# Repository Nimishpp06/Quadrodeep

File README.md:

# QuadroDeep — Smart Attendance System

> **K. J. Somaiya Institute of Technology** — Academic IoT Project

A full-stack IoT attendance management system for academic lab environments. Combines **ESP32-based hardware** (RFID + Fingerprint) with a **Node.js backend** and **role-based web dashboards** for students, professors, and administrators.

---

## Table of Contents

- [Architecture](#architecture)
- [Features](#features)
- [Tech Stack](#tech-stack)
- [Hardware Pinout](#hardware-pinout)
- [Project Structure](#project-structure)
- [Getting Started](#getting-started)
- [Configuration](#configuration)
- [API Endpoints](#api-endpoints)
- [Team](#team)

---

## Architecture

```
┌─────────────────────────────────────────────────────────┐
│                    Frontend (Browser)                    │
│  Student Dashboard · Professor Dashboard · Admin View    │
└──────────────────────┬──────────────────────────────────┘
                       │ HTTP REST
┌──────────────────────▼──────────────────────────────────┐
│              Node.js Backend (Express)                   │
│  Authentication · Analytics · Session Management · MQTT  │
└──────┬───────────────────────────────┬──────────────────┘
       │ MQTT Pub/Sub                  │ REST
┌──────▼──────┐                 ┌──────▼──────────────────┐
│  ESP32 Node │  ◄──────────── │     Supabase (PostgreSQL) │
│  (RFID+FP)  │  light sleep   │  Attendance · Users · Labs │
└─────────────┘   wake-on-IR   └─────────────────────────┘
```

---

## Features

### Student View
- **Attendance gauge** with color-coded eligibility (≥75% green, <75% red)
- **"Can miss" counter** — how many more classes before falling below threshold
- **Punctuality tracking** — on-time vs late arrival breakdown
- **Verification mode chart** — RFID vs Fingerprint preference
- **Check-in history** — last 20 entries with status badges

### Professor View
- **Live session turnout** — present / total per session
- **Attendance trends** — 30-day line chart
- **Mode adoption pie** — RFID vs Fingerprint usage
- **At-risk flagging** — students with >15% attendance drop over 2 weeks
- **Arrival heatmap** — time-of-day distribution

### Admin View
- **Device fleet monitor** — online / offline / sleep per lab
- **Hardware alerts** — low memory, sensor errors, MQTT drops
- **Enrollment matrix** — students onboarded vs RFID vs biometric
- **Bypass audit log** — force-initialized sessions outside timetable
- **Global attendance rate** with most-utilized lab

### Hardware Capabilities
- Dual-factor authentication (RFID + Fingerprint)
- Light sleep after 5 min idle — wakes on IR motion or button press
- UART state preserved across sleep (no fingerprint re-init)
- Common-anode RGB status indicator
- Standalone offline queue with JSON storage on SPIFFS

---

## Tech Stack

| Layer | Technology |
|-------|-----------|
| **Firmware** | Arduino / C++ (ESP32) |
| **Backend** | Node.js + Express |
| **Database** | Supabase (PostgreSQL) |
| **Frontend** | Vanilla JS + Chart.js |
| **Messaging** | MQTT (Mosquitto) |
| **Biometrics** | R307 / AS608 Fingerprint Scanner |
| **RFID** | MFRC522 |
| **Display** | I2C LCD 16×2 |
| **Power** | Light sleep (ESP32 deep sleep variant) |

---

## Hardware Pinout

| Component | ESP32 Pin | Bus |
|-----------|-----------|-----|
| RFID RST | GPIO 4 | — |
| RFID MISO | GPIO 19 | SPI |
| RFID MOSI | GPIO 23 | SPI |
| RFID SCK | GPIO 18 | SPI |
| RFID SDA/SS | GPIO 5 | SPI |
| Fingerprint RX (ESP TX2) | GPIO 17 | UART2 |
| Fingerprint TX (ESP RX2) | GPIO 16 | UART2 |
| Buzzer | GPIO 14 | — |
| IR / PIR Motion | GPIO 33 | — (wake source) |
| Push Button | GPIO 32 | — (wake source) |
| I2C SDA | GPIO 21 | I2C |
| I2C SCL | GPIO 22 | I2C |
| RGB Red | GPIO 27 | Common anode |
| RGB Green | GPIO 26 | Common anode |
| RGB Blue | GPIO 25 | Common anode |

---

## Project Structure

```
QuadroDeep/
├── QuadroDeep_Node/          # ESP32 firmware
│   ├── QuadroDeep_Node.ino   # Main state machine
│   ├── config.h              # Pins, WiFi, MQTT, API base
│   ├── hardware.h            # Init / wake / sleep helpers
│   ├── wifi_manager.h        # WiFi provisioning
│   ├── storage.h             # SPIFFS offline queue
│   └── device_base64.h       # Base64 fingerprint templates
├── backend/                  # Node.js server
│   ├── server.js             # Express app + routes
│   ├── jobs/                 # Cron jobs (reminders)
│   ├── services/             # Notification service
│   ├── templates/            # Email templates
│   ├── utils/                # Helpers (Resend, retry)
│   ├── package.json
│   └── .env.example          # Required environment variables
├── index.html                # Web dashboard
├── QuadroDeep-Logo.png
└── somaiya-logo.png
```

---

## Getting Started

### Prerequisites

- Node.js v18+
- Supabase (PostgreSQL) project
- Mosquitto MQTT broker
- ESP32 with Arduino IDE
- R307 / AS608 fingerprint sensor + MFRC522 RFID module

### Backend

```bash
cd backend
cp .env.example .env    # Edit with your credentials
npm install
node server.js
```

### ESP32 Firmware

1. Open `QuadroDeep_Node/QuadroDeep_Node.ino` in Arduino IDE
2. Install libraries: `MFRC522`, `Adafruit_Fingerprint`, `LiquidCrystal_I2C`, `PubSubClient`, `ArduinoJson`
3. Edit `config.h`:
   - Set `WIFI_SSID` / `WIFI_PASSWORD`
   - Set `API_BASE` to your backend IP
   - Set `MQTT_BROKER` to your broker IP
4. Upload to ESP32

### Frontend

Serve `index.html` via Live Server (port 5501) or any static server.

---

## Configuration

### Backend (`backend/.env`)

| Variable | Description |
|----------|-------------|
| `PORT` | Server port (default: 3000) |
| `SUPABASE_URL` | Supabase project URL |
| `SUPABASE_SERVICE_KEY` | Supabase service-role JWT |
| `MQTT_BROKER_URL` | `mqtt://<broker-ip>:1885` |
| `RESEND_API_KEY` | Resend email API key |
| `FROM_EMAIL` | Sender email address |

### ESP32 (`QuadroDeep_Node/config.h`)

| Constant | Description |
|----------|-------------|
| `API_BASE` | Backend URL (e.g. `http://192.168.1.100:3000`) |
| `LAB_ID` | Lab identifier (e.g. `IOT_01`) |
| `WIFI_SSID` | WiFi network name |
| `WIFI_PASSWORD` | WiFi password |
| `MQTT_BROKER` | Broker IP address |

---

## API Endpoints

| Method | Endpoint | Role | Purpose |
|--------|----------|------|---------|
| `GET` | `/api/analytics/student/:id` | Student | Attendance %, eligibility, punctuality, mode pie, history |
| `GET` | `/api/analytics/professor/dashboard` | Professor | Session stats, 30-day trends, at-risk list, mode split |
| `GET` | `/api/analytics/professor/heatmap` | Professor | Arrival time bucket distribution |
| `GET` | `/api/analytics/admin/overview` | Admin | Users, labs, devices, attendance rate, alerts |
| `GET` | `/api/analytics/admin/enrollment-progress` | Admin | RFID vs biometric onboarding |
| `GET` | `/api/analytics/admin/bypass-log` | Admin | Force-init session audit trail |

---

## Adafruit Fingerprint Library Patch

This project uses a patched version of `Adafruit_Fingerprint` that adds **UPCHAR / DOWNCHAR** support for raw template upload and download — enabling fingerprint backup, restore, and sensor cloning.

The patched library files are in [`adafruit-patch/`](./adafruit-patch/), and also maintained as a standalone repository:
**[github.com/Nimishpp06/adafruit-fingerprint-updown](https://github.com/Nimishpp06/adafruit-fingerprint-updown)**

---

## Team

- **Nimish Patil**
- **Ashley Dsilva**
- **Sweekar Mandavkar**
- **Dhruv Maurya**

**K. J. Somaiya school of engineering, Vidyavihar Mumbai**

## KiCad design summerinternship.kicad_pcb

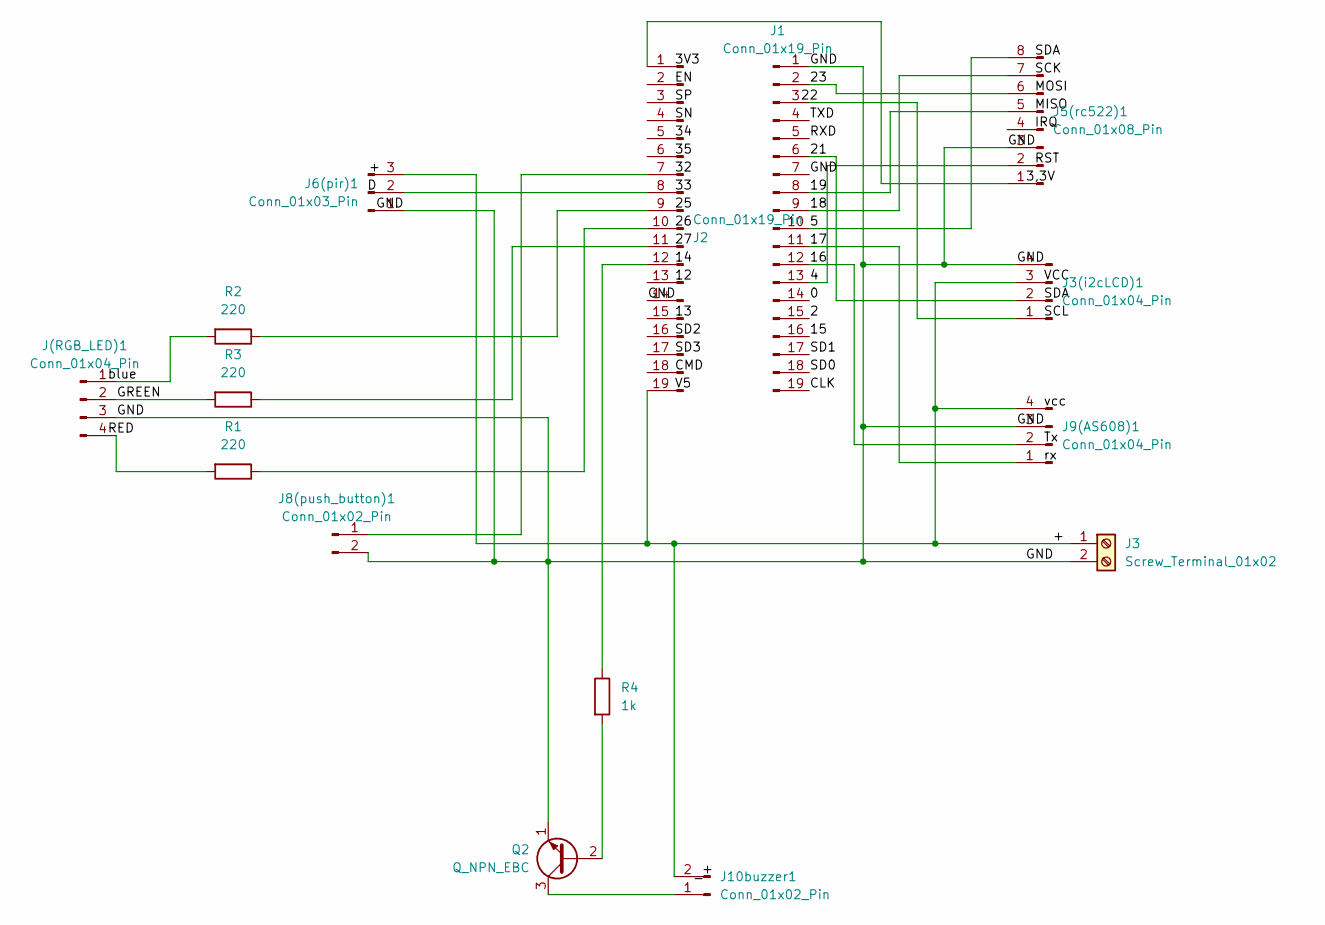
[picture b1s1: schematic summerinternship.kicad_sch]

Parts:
J1, J2: Conn_01x19_Pin; PinHeader_1x19_P2.54mm_Vertical
J3: Screw_Terminal_01x02; TerminalBlock_MaiXu_MX126-5.0-02P_1x02_P5.00mm
J3(i2cLCD)1, J9(AS608)1: Conn_01x04_Pin; PinHeader_1x04_P2.54mm_Vertical
J5(rc522)1: Conn_01x08_Pin; PinSocket_1x08_P2.54mm_Vertical
J6(pir)1: Conn_01x03_Pin; PinHeader_1x03_P2.54mm_Vertical
J8(push_button)1, J10buzzer1: Conn_01x02_Pin; PinHeader_1x02_P2.54mm_Vertical
J(RGB_LED)1: Conn_01x04_Pin; PinHeader_1x04_P2.54mm_Vertical
Q2: Q_NPN_EBC; PinHeader_1x03_P2.54mm_Vertical
R1, R2, R3: 220; R_Axial_DIN0207_L6.3mm_D2.5mm_P7.62mm_Horizontal
R4: 1k; R_Axial_DIN0207_L6.3mm_D2.5mm_P7.62mm_Horizontal

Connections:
/0: J1.14
/2: J1.15
/4: J1.13, J5(rc522)1.2
/5: J1.10, J5(rc522)1.8
/15: J1.16
/16: J1.12, J9(AS608)1.2
/17: J1.11, J9(AS608)1.1
/18: J1.9, J5(rc522)1.7
/19: J1.8, J5(rc522)1.5
/21: J1.6, J3(i2cLCD)1.2
/23: J1.2, J5(rc522)1.6
/+: J2.19, J3.1, J3(i2cLCD)1.3, J6(pir)1.3, J9(AS608)1.4, J10buzzer1.2
/CLK: J1.19
/GND: J1.1, J1.7, J2.14, J3.2, J3(i2cLCD)1.4, J5(rc522)1.3, J6(pir)1.1, J8(push_button)1.2, J9(AS608)1.3, J(RGB_LED)1.3, Q2.1 (E)
/GREEN: J(RGB_LED)1.2, R3.2
/RXD: J1.5
/SD0: J1.18
/SD1: J1.17
/TXD: J1.4
unnamed: J1.3, J3(i2cLCD)1.1
unnamed: J2.1, J5(rc522)1.1
unnamed: J2.7, J8(push_button)1.1
unnamed: J2.8, J6(pir)1.2
unnamed: J2.9, R2.1
unnamed: J2.10, R1.1
unnamed: J2.11, R3.1
unnamed: J2.12, R4.1
unnamed: J10buzzer1.1, Q2.3 (C)
unnamed: J(RGB_LED)1.1, R2.2
unnamed: J(RGB_LED)1.4, R1.2
unnamed: Q2.2 (B), R4.2

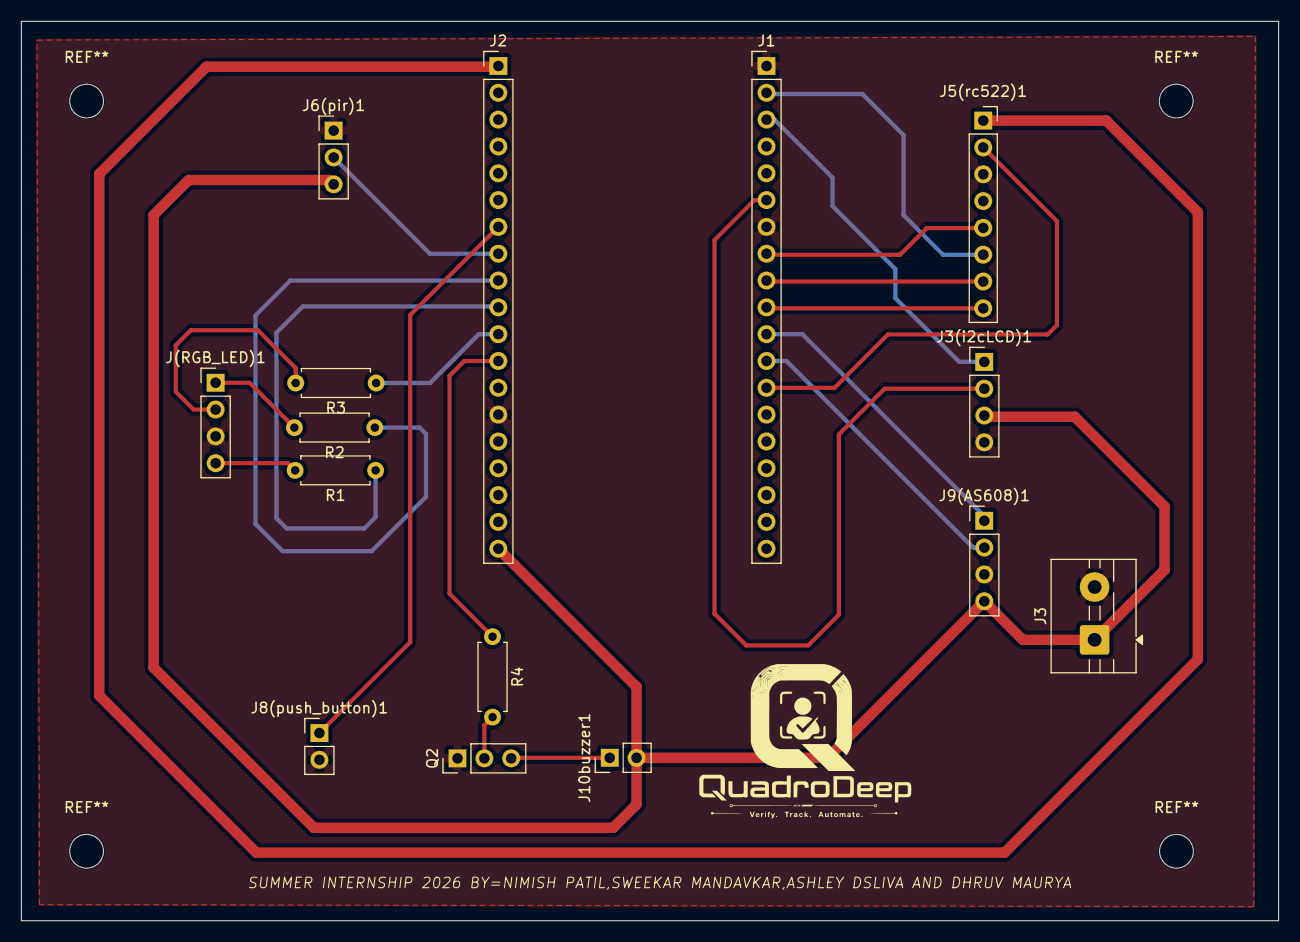
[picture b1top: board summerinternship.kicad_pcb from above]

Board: 2 copper layers, 119.1 x 85.2 mm, 15 parts (0 on the bottom side), 23 nets.

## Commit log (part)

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2026-06-02 Revise README.md for Quadrodeep project
    Updated project description and added key features, system architecture, repository structure, and development team information.
